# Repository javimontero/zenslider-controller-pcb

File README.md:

# ZenSlider Controller PCB
Motion control controller based on ATMEGA644p microcontroller.

Eagle schematics and PCB for [ZenSlider and ZenFocus](http://zenslider.com) controller

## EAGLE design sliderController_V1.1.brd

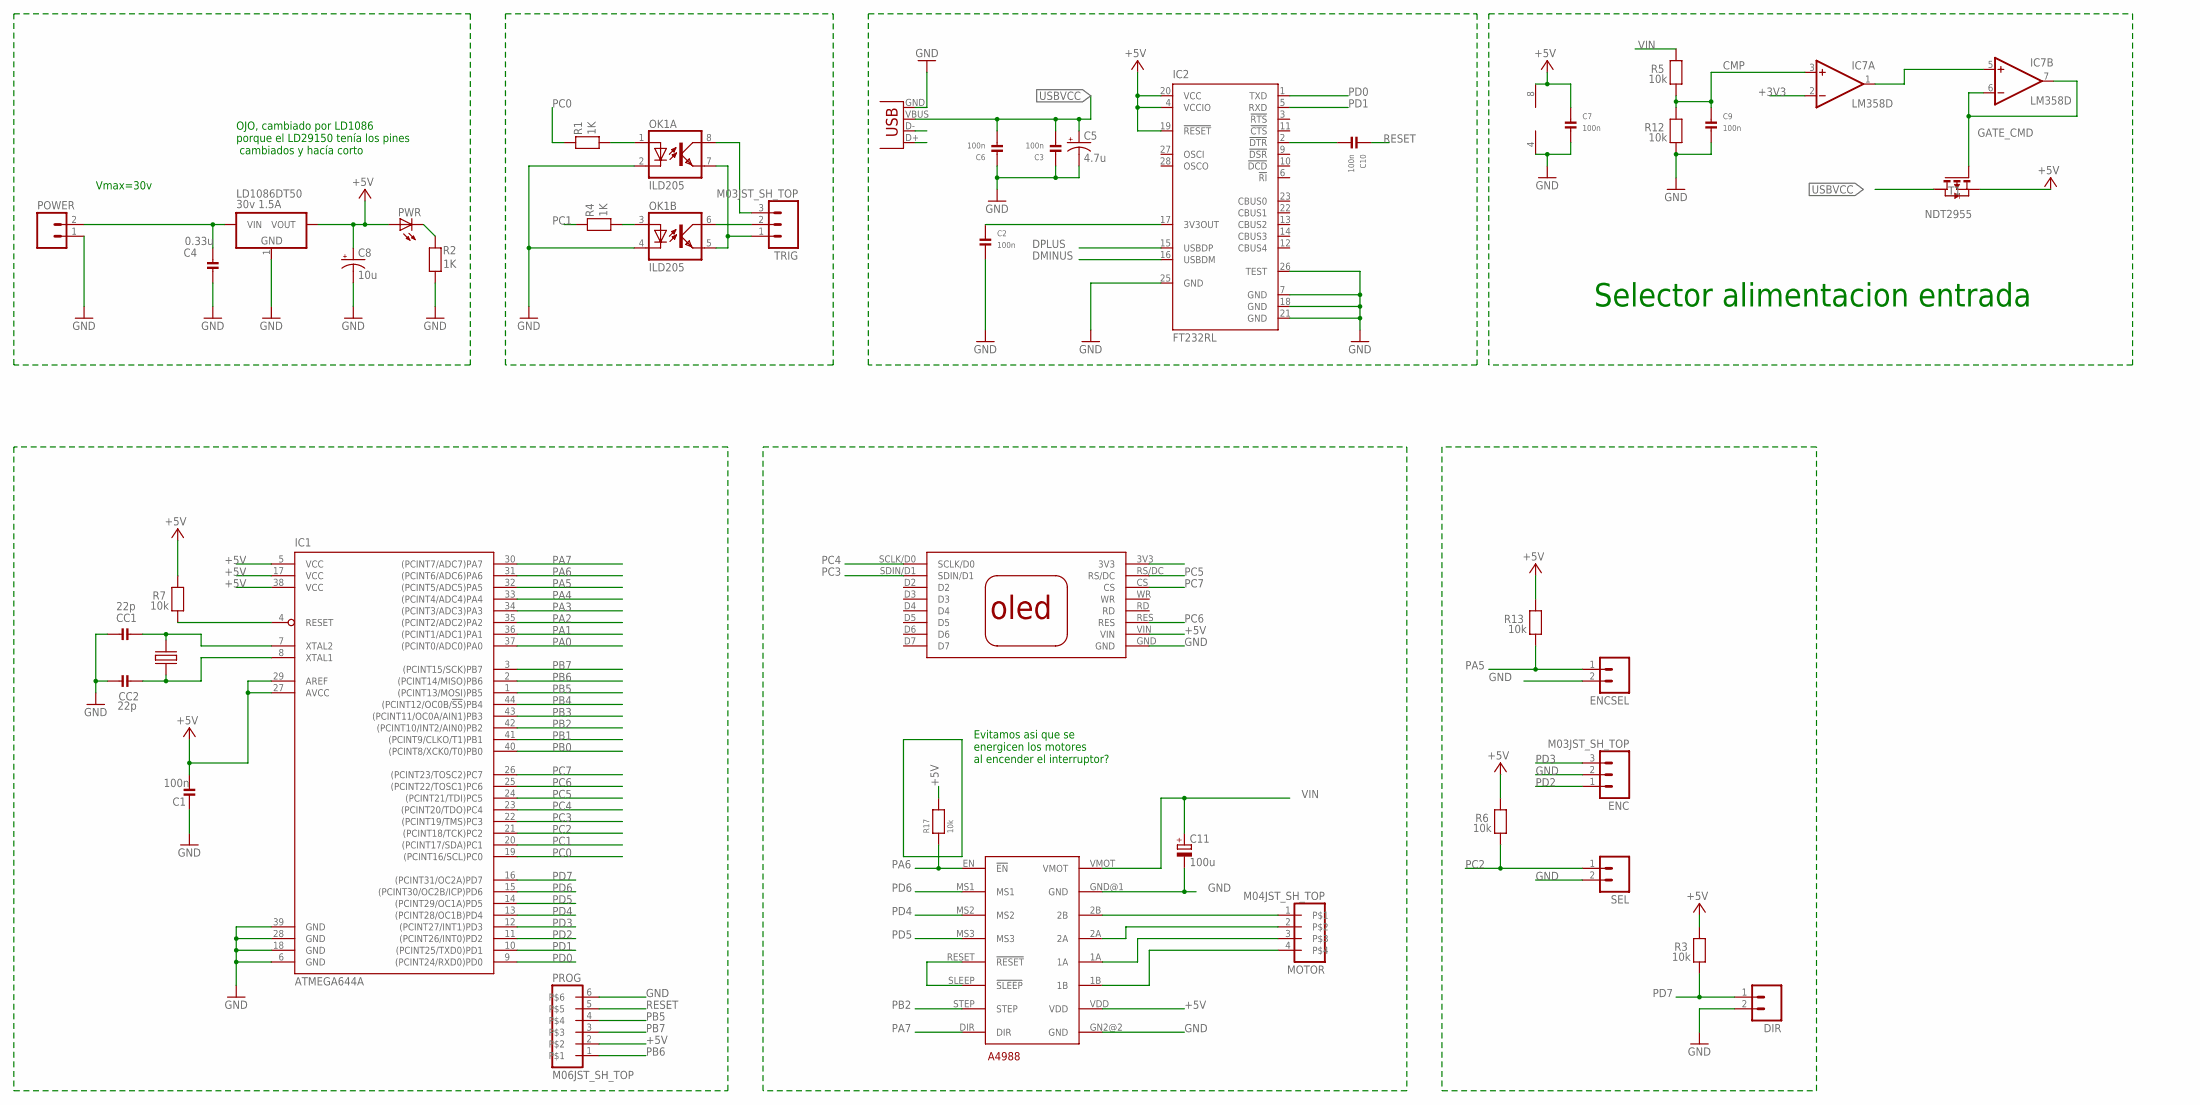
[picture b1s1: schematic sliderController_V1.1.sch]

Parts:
A4988: STEPSTICK_A4988A4988; STEPSTICK_A4988
C1, C2, C3, C6, C10: 100n; _0805
C4: 0.33u; _0805
C5: 4.7u; EIA3216
C7, C9: 100n; 0805
C8: 10u; EIA3216
C11: 100u; PANASONIC_D
CC1, CC2: 22p; _0805
CRISTAL: CRISTALSMD; CRISTAL5X3.2MM
DIR: M02JST_SH_TOP; JST_1.0_2_TOP
ENC: M03JST_SH_TOP; JST_1.0_3_TOP
ENCSEL: M02JST_SH_TOP; JST_1.0_2_TOP
IC1: ATMEGA644A; TQFP44
IC2: FT232RL; SSOP28
IC7: LM358D; SO08
LD1086DT50: 30v 1.5A; DPAK
MOTOR: M04JST_SH_TOP; JST_1.0_4_TOP
OK1: ILD205; SOIC08
POWER: M02JST_SH_TOP; JST_1.0_2_TOP
PROG: M06JST_SH_TOP; JST_1.0_6_TOP
PWR: LEDCHIP-LED0805; CHIP-LED0805
R1, R2, R4: 1K; 0805
R3, R5, R6, R7, R12, R13, R17: 10k; 0805
SEL: M02JST_SH_TOP; JST_1.0_2_TOP
T1: NDT2955; SOT223
TRIG: M03JST_SH_TOP; JST_1.0_3_TOP
U$3: OLEDOLED1.3"; OLED1.3"
X2: USBSMD; USB-MINIB

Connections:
+3V3: C2.1, IC2.17 (3V3OUT), IC7.2 (-IN)
+5V: A4988.VDD, C1.2, C7.1, C8.A (+), IC1.5 (VCC), IC1.17 (VCC), IC1.27 (AVCC), IC1.29 (AREF), IC1.38 (VCC), IC2.4 (VCCIO), IC2.19 (!RESET), IC2.20 (VCC), IC7.8 (V+), LD1086DT50.2 (VOUT), PROG.2, PWR.A, R3.2, R6.2, R7.2, R13.2, R17.2, T1.3 (S), U$3.VIN
CMP: C9.1, IC7.3 (+IN), R5.1, R12.2
DMINUS: IC2.16 (USBDM), X2.D-
DPLUS: IC2.15 (USBDP), X2.D+
GATE_CMD: IC7.6 (-IN), IC7.7 (OUT), T1.1 (G)
GND: A4988.GN2@2 (GND), A4988.GND@1 (GND), C1.1, C2.2, C3.1, C4.1, C5.C (-), C6.1, C7.2, C8.C (-), C9.2, C11.-, CC1.1, CC2.1, DIR.2, ENC.2, ENCSEL.2, IC1.6 (GND), IC1.18 (GND), IC1.28 (GND), IC1.39 (GND), IC2.7 (GND), IC2.18 (GND), IC2.21 (GND), IC2.25 (GND), IC2.26 (TEST), IC7.4 (V-), LD1086DT50.1 (GND), OK1.2 (C), OK1.4 (C), POWER.1, PROG.6, R2.2, R12.1, SEL.2, U$3.GND, X2.GND
unnamed: C10.2, IC2.2 (!DTR)
unnamed: PWR.C, R2.1
unnamed: CC1.2, CRISTAL.B, IC1.7 (XTAL2)
unnamed: A4988.RESET (!RESET), A4988.SLEEP (!SLEEP)
unnamed: OK1.1 (A), R1.2
unnamed: OK1.8 (COL), TRIG.3
unnamed: OK1.6 (COL), TRIG.2
unnamed: OK1.5 (EMIT), OK1.7 (EMIT), TRIG.1
unnamed: A4988.2B, MOTOR.1
unnamed: CC2.2, CRISTAL.A, IC1.8 (XTAL1)
unnamed: OK1.3 (A), R4.2
unnamed: A4988.2A, MOTOR.2
unnamed: A4988.1A, MOTOR.3
unnamed: A4988.1B, MOTOR.4
unnamed: IC7.1 (OUT), IC7.5 (+IN)
PA0: IC1.37 ((PCINT0/ADC0)PA0)
PA1: IC1.36 ((PCINT1/ADC1)PA1)
PA2: IC1.35 ((PCINT2/ADC2)PA2)
PA3: IC1.34 ((PCINT3/ADC3)PA3)
PA4: IC1.33 ((PCINT4/ADC4)PA4)
PA5: ENCSEL.1, IC1.32 ((PCINT5/ADC5)PA5), R13.1
PA6: A4988.EN (!EN), IC1.31 ((PCINT6/ADC6)PA6), R17.1
PA7: A4988.DIR, IC1.30 ((PCINT7/ADC7)PA7)
PB0: IC1.40 ((PCINT8/XCK0/T0)PB0)
PB1: IC1.41 ((PCINT9/CLKO/T1)PB1)
PB2: A4988.STEP, IC1.42 ((PCINT10/INT2/AIN0)PB2)
PB3: IC1.43 ((PCINT11/OC0A/AIN1)PB3)
PB4: IC1.44 ((PCINT12/OC0B/!SS!)PB4)
PB5: IC1.1 ((PCINT13/MOSI)PB5), PROG.4
PB6: IC1.2 ((PCINT14/MISO)PB6), PROG.1
PB7: IC1.3 ((PCINT15/SCK)PB7), PROG.3
PC0: IC1.19 ((PCINT16/SCL)PC0), R1.1
PC1: IC1.20 ((PCINT17/SDA)PC1), R4.1
PC2: IC1.21 ((PCINT18/TCK)PC2), R6.1, SEL.1
PC3: IC1.22 ((PCINT19/TMS)PC3), U$3.SDIN/D1
PC4: IC1.23 ((PCINT20/TDO)PC4), U$3.SCLK/D0
PC5: IC1.24 ((PCINT21/TDI)PC5), U$3.RS/DC
PC6: IC1.25 ((PCINT22/TOSC1)PC6), U$3.RES
PC7: IC1.26 ((PCINT23/TOSC2)PC7), U$3.CS
PD0: IC1.9 ((PCINT24/RXD0)PD0), IC2.1 (TXD)
PD1: IC1.10 ((PCINT25/TXD0)PD1), IC2.5 (RXD)
PD2: ENC.1, IC1.11 ((PCINT26/INT0)PD2)
PD3: ENC.3, IC1.12 ((PCINT27/INT1)PD3)
PD4: A4988.MS2, IC1.13 ((PCINT28/OC1B)PD4)
PD5: A4988.MS3, IC1.14 ((PCINT29/OC1A)PD5)
PD6: A4988.MS1, IC1.15 ((PCINT30/OC2B/ICP)PD6)
PD7: DIR.1, IC1.16 ((PCINT31/OC2A)PD7), R3.1
RESET: C10.1, IC1.4 (RESET), PROG.5, R7.1
USBVCC: C3.2, C5.A (+), C6.2, T1.2 (D), X2.VBUS
VIN: A4988.VMOT, C4.2, C11.+, LD1086DT50.3 (VIN), POWER.2, R5.2

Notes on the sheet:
Vmax=30v
OJO, cambiado por LD1086 porque el LD29150 tenía los pines cambiados y hacía corto
Evitamos asi que se energicen los motores al encender el interruptor?
Selector alimentacion entrada

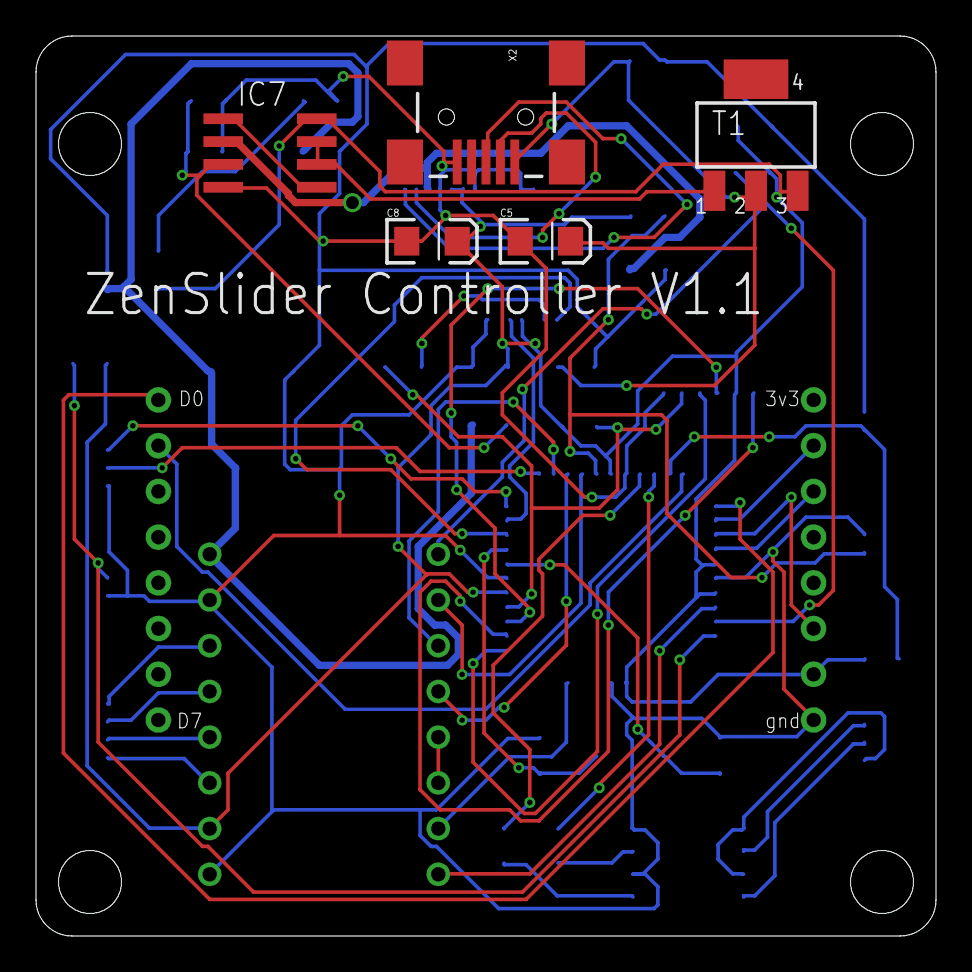
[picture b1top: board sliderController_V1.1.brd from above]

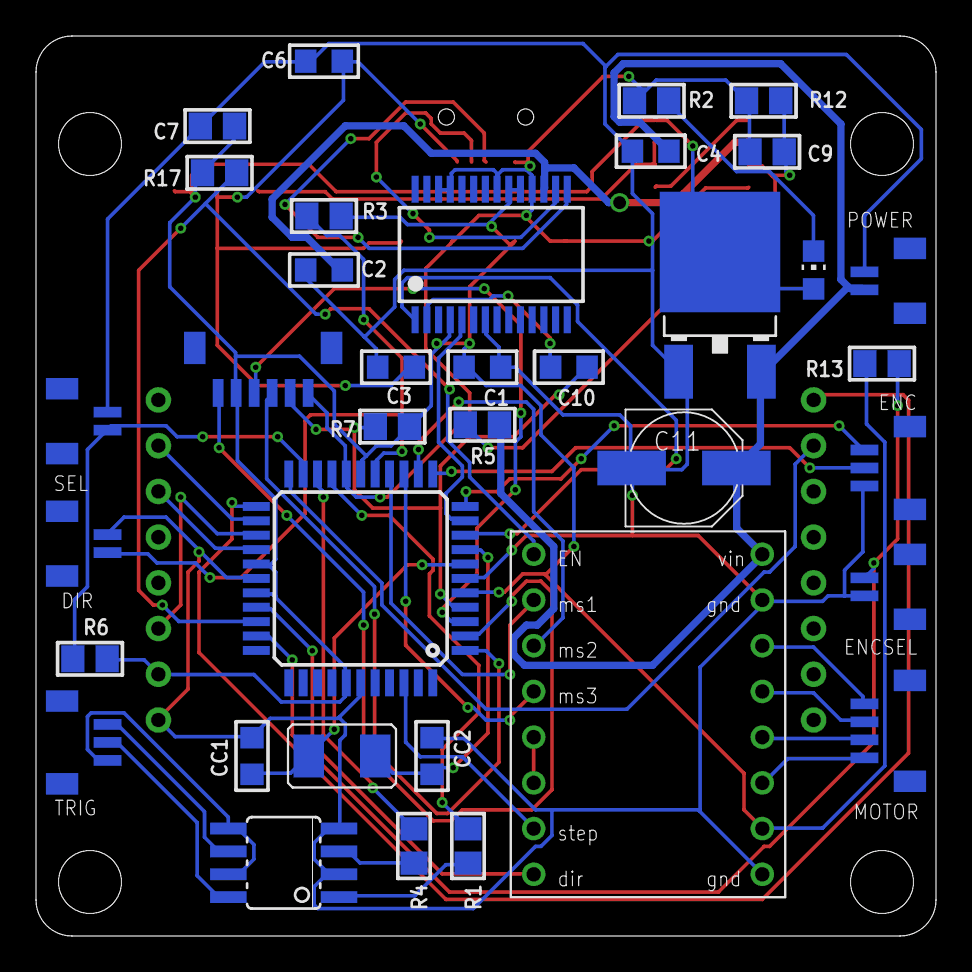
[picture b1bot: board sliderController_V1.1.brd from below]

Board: 2 copper layers, 50.0 x 50.0 mm, 42 parts (36 on the bottom side), 48 nets.

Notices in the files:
parts and their libraries:
SparkFun-Passives: Licensing: CC v3.0 Share-Alike You are welcome to use this library for commercial purposes.
microbuilder: This work is placed in the public domain, and may be freely used for commercial and non-commercial work with the following conditions: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
